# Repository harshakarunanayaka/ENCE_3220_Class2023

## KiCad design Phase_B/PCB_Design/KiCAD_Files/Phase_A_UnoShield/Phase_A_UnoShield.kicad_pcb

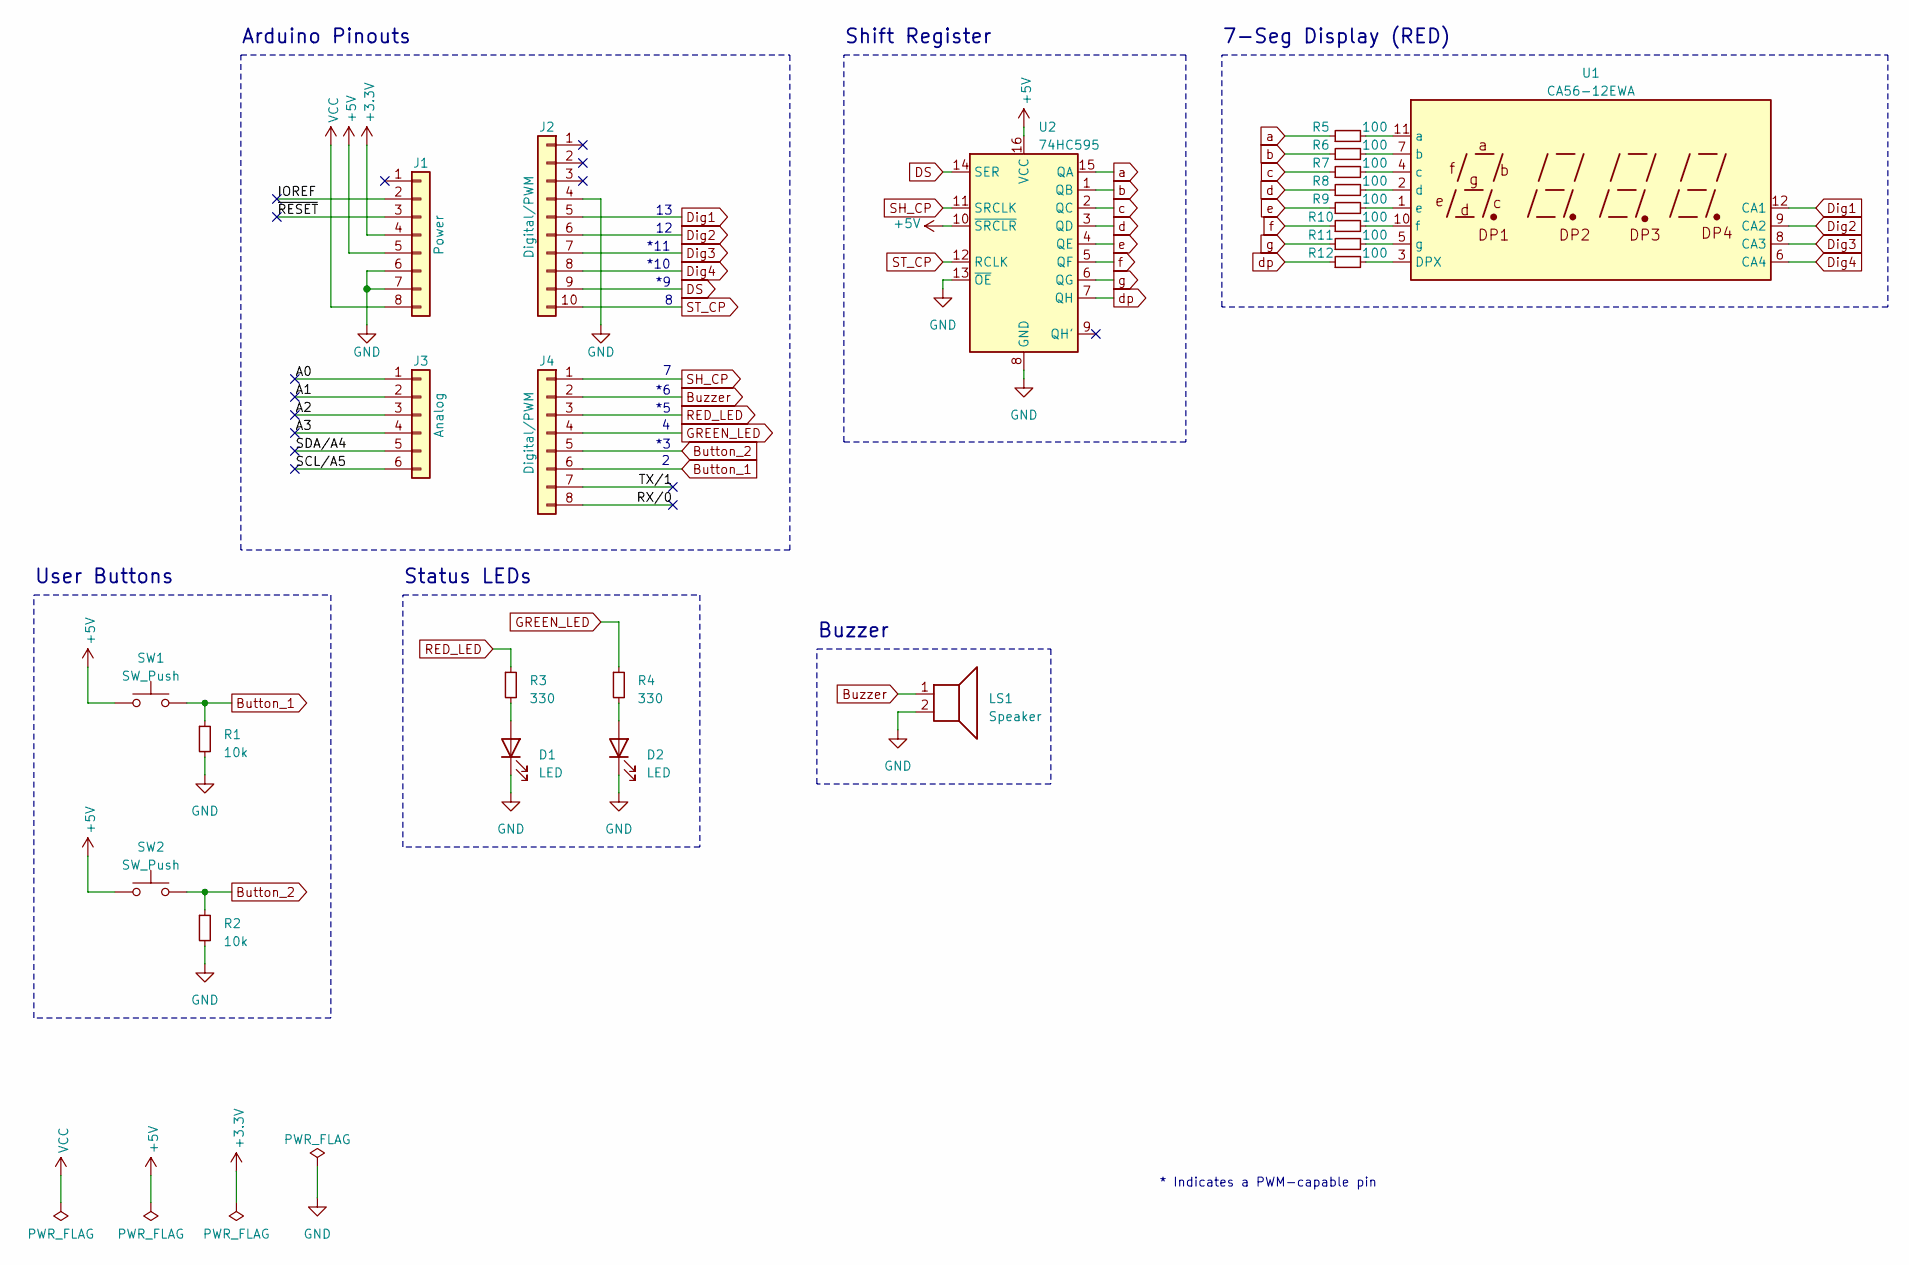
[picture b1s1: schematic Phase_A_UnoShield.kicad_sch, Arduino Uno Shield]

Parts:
D1, D2: LED; LED_D5.0mm
J1: Power; PinSocket_1x08_P2.54mm_Vertical
J2: Digital/PWM; PinSocket_1x10_P2.54mm_Vertical
J3: Analog; PinSocket_1x06_P2.54mm_Vertical
J4: Digital/PWM; PinSocket_1x08_P2.54mm_Vertical
LS1: Speaker; Buzzer_12x9.5RM7.6
R1, R2: 10k; R_Axial_DIN0207_L6.3mm_D2.5mm_P10.16mm_Horizontal
R3, R4: 330; R_Axial_DIN0207_L6.3mm_D2.5mm_P10.16mm_Horizontal
R5, R6, R7, R8, R9, R10, R11, R12: 100; R_Axial_DIN0207_L6.3mm_D2.5mm_P10.16mm_Horizontal
SW1, SW2: SW_Push; SW_PUSH-12mm
U1: CA56-12EWA
U2: 74HC595; DIP-16_W7.62mm_Socket_LongPads

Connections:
+3V3: J1.4
+5V: J1.5, SW1.1, SW2.1, U2.10 (~SRCLR), U2.16 (VCC)
/A0: J3.1
/A1: J3.2
/A2: J3.3
/A3: J3.4
/IOREF: J1.2
/RX/0: J4.8
/SCL/A5: J3.6
/SDA/A4: J3.5
/TX/1: J4.7
/~RESET: J1.3
Button_1: J4.6, R1.1, SW1.2
Button_2: J4.5, R2.1, SW2.2
Buzzer: J4.2, LS1.1
DS: J2.9, U2.14 (SER)
Dig1: J2.5, U1.12 (CA1)
Dig2: J2.6, U1.9 (CA2)
Dig3: J2.7, U1.8 (CA3)
Dig4: J2.8, U1.6 (CA4)
GND: D1.1 (K), D2.1 (K), J1.6, J1.7, J2.4, LS1.2, R1.2, R2.2, U2.8 (GND), U2.13 (~OE)
GREEN_LED: J4.4, R4.1
unnamed: D1.2 (A), R3.2
unnamed: D2.2 (A), R4.2
unnamed: R12.2, U1.3 (DPX)
unnamed: R5.2, U1.11 (a)
unnamed: R6.2, U1.7 (b)
unnamed: R7.2, U1.4 (c)
unnamed: R8.2, U1.2 (d)
unnamed: R9.2, U1.1 (e)
unnamed: R10.2, U1.10 (f)
unnamed: R11.2, U1.5 (g)
RED_LED: J4.3, R3.1
SH_CP: J4.1, U2.11 (SRCLK)
ST_CP: J2.10, U2.12 (RCLK)
VCC: J1.8
a: R5.1, U2.15 (QA)
b: R6.1, U2.1 (QB)
c: R7.1, U2.2 (QC)
d: R8.1, U2.3 (QD)
dp: R12.1, U2.7 (QH)
e: R9.1, U2.4 (QE)
f: R10.1, U2.5 (QF)
g: R11.1, U2.6 (QG)

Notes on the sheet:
Shift Register
*10
Status LEDs
Arduino Pinouts
User Buttons
Buzzer
* Indicates a PWM-capable pin
7-Seg Display (RED)
*11

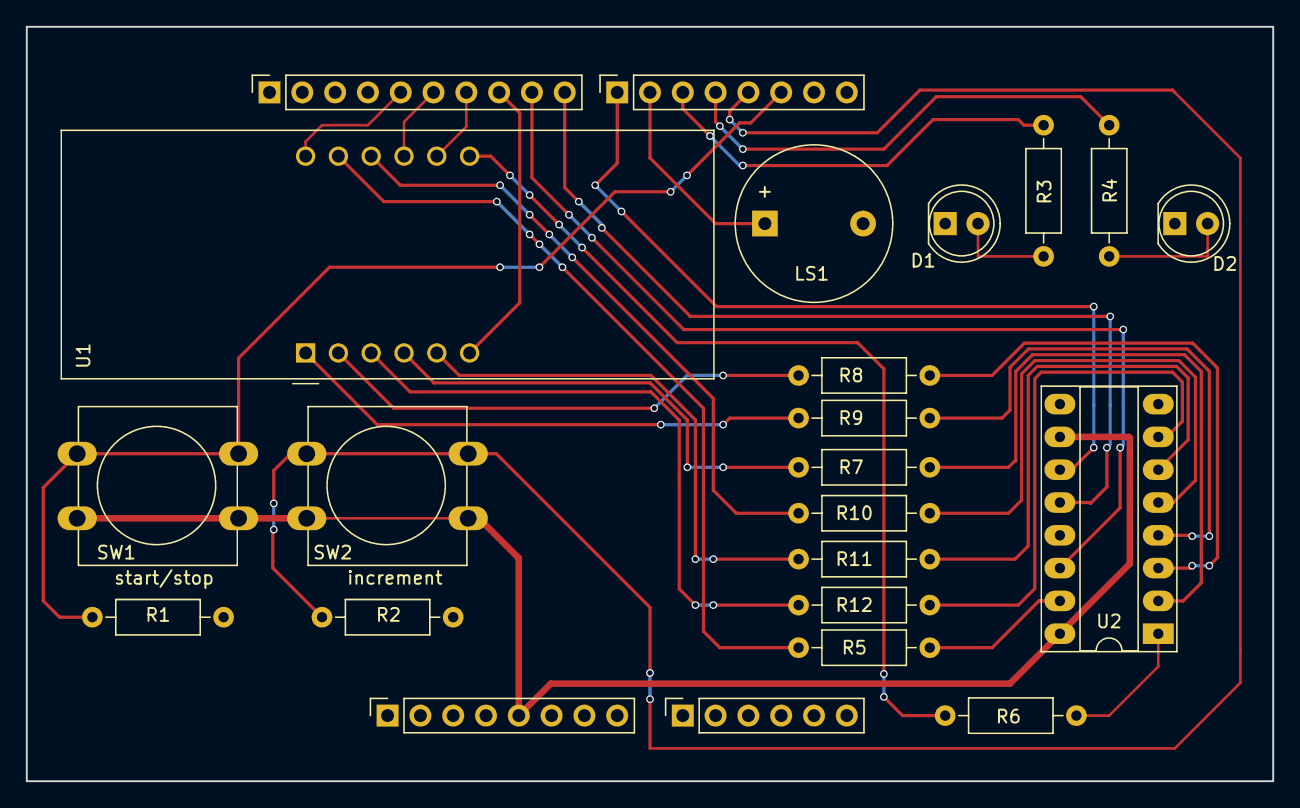
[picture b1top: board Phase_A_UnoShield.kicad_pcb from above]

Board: 2 copper layers, 96.5 x 58.4 mm, 23 parts (0 on the bottom side), 32 nets.

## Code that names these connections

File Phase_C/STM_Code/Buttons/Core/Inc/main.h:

/* USER CODE BEGIN Header */
/**
  ******************************************************************************
  * @file           : main.h
  * @brief          : Header for main.c file.
  *                   This file contains the common defines of the application.
  ******************************************************************************
  * @attention
  *
  * Copyright (c) 2023 STMicroelectronics.
  * All rights reserved.
  *
  * This software is licensed under terms that can be found in the LICENSE file
  * in the root directory of this software component.
  * If no LICENSE file comes with this software, it is provided AS-IS.
  *
  ******************************************************************************
  */
/* USER CODE END Header */

/* Define to prevent recursive inclusion -------------------------------------*/
#ifndef __MAIN_H
#define __MAIN_H

#ifdef __cplusplus
extern "C" {
#endif

/* Includes ------------------------------------------------------------------*/
#include "stm32f4xx_hal.h"

/* Private includes ----------------------------------------------------------*/
/* USER CODE BEGIN Includes */

/* USER CODE END Includes */

/* Exported types ------------------------------------------------------------*/
/* USER CODE BEGIN ET */

/* USER CODE END ET */

/* Exported constants --------------------------------------------------------*/
/* USER CODE BEGIN EC */

/* USER CODE END EC */

/* Exported macro ------------------------------------------------------------*/
/* USER CODE BEGIN EM */

/* USER CODE END EM */

/* Exported functions prototypes ---------------------------------------------*/
void Error_Handler(void);

/* USER CODE BEGIN EFP */

/* USER CODE END EFP */

/* Private defines -----------------------------------------------------------*/
#define CS_I2C_SPI_Pin GPIO_PIN_3
#define CS_I2C_SPI_GPIO_Port GPIOE
#define PC14_OSC32_IN_Pin GPIO_PIN_14
#define PC14_OSC32_IN_GPIO_Port GPIOC
#define PC15_OSC32_OUT_Pin GPIO_PIN_15
#define PC15_OSC32_OUT_GPIO_Port GPIOC
#define PH0_OSC_IN_Pin GPIO_PIN_0
#define PH0_OSC_IN_GPIO_Port GPIOH
#define PH1_OSC_OUT_Pin GPIO_PIN_1
#define PH1_OSC_OUT_GPIO_Port GPIOH
#define OTG_FS_PowerSwitchOn_Pin GPIO_PIN_0
#define OTG_FS_PowerSwitchOn_GPIO_Port GPIOC
#define PDM_OUT_Pin GPIO_PIN_3
#define PDM_OUT_GPIO_Port GPIOC
#define B1_Pin GPIO_PIN_0
#define B1_GPIO_Port GPIOA
#define B1_EXTI_IRQn EXTI0_IRQn
#define I2S3_WS_Pin GPIO_PIN_4
#define I2S3_WS_GPIO_Port GPIOA
#define SPI1_SCK_Pin GPIO_PIN_5
#define SPI1_SCK_GPIO_Port GPIOA
#define SPI1_MISO_Pin GPIO_PIN_6
#define SPI1_MISO_GPIO_Port GPIOA
#define SPI1_MOSI_Pin GPIO_PIN_7
#define SPI1_MOSI_GPIO_Port GPIOA
#define BUTTON_1_Pin GPIO_PIN_4
#define BUTTON_1_GPIO_Port GPIOC
#define BUTTON_1_EXTI_IRQn EXTI4_IRQn
#define BUTTON_2_Pin GPIO_PIN_5
#define BUTTON_2_GPIO_Port GPIOC
#define BUTTON_2_EXTI_IRQn EXTI9_5_IRQn
#define GREEN_LED_Pin GPIO_PIN_0
#define GREEN_LED_GPIO_Port GPIOB
#define RED_LED_Pin GPIO_PIN_1
#define RED_LED_GPIO_Port GPIOB
#define BOOT1_Pin GPIO_PIN_2
#define BOOT1_GPIO_Port GPIOB
#define CLOCK_Pin GPIO_PIN_7
#define CLOCK_GPIO_Port GPIOE
#define LATCH_Pin GPIO_PIN_8
#define LATCH_GPIO_Port GPIOE
#define DATA_Pin GPIO_PIN_9
#define DATA_GPIO_Port GPIOE
#define DIG4_Pin GPIO_PIN_11
#define DIG4_GPIO_Port GPIOE
#define DIG3_Pin GPIO_PIN_12
#define DIG3_GPIO_Port GPIOE
#define DIG2_Pin GPIO_PIN_13
#define DIG2_GPIO_Port GPIOE
#define DIG1_Pin GPIO_PIN_14
#define DIG1_GPIO_Port GPIOE
#define CLK_IN_Pin GPIO_PIN_10
#define CLK_IN_GPIO_Port GPIOB
#define LD4_Pin GPIO_PIN_12
#define LD4_GPIO_Port GPIOD
#define LD3_Pin GPIO_PIN_13
#define LD3_GPIO_Port GPIOD
#define LD5_Pin GPIO_PIN_14
#define LD5_GPIO_Port GPIOD
#define LD6_Pin GPIO_PIN_15
#define LD6_GPIO_Port GPIOD
#define I2S3_MCK_Pin GPIO_PIN_7
#define I2S3_MCK_GPIO_Port GPIOC
#define VBUS_FS_Pin GPIO_PIN_9
#define VBUS_FS_GPIO_Port GPIOA
#define OTG_FS_ID_Pin GPIO_PIN_10
#define OTG_FS_ID_GPIO_Port GPIOA
#define OTG_FS_DM_Pin GPIO_PIN_11
#define OTG_FS_DM_GPIO_Port GPIOA
#define OTG_FS_DP_Pin GPIO_PIN_12
#define OTG_FS_DP_GPIO_Port GPIOA
#define SWDIO_Pin GPIO_PIN_13
#define SWDIO_GPIO_Port GPIOA
#define SWCLK_Pin GPIO_PIN_14
#define SWCLK_GPIO_Port GPIOA
#define I2S3_SCK_Pin GPIO_PIN_10
#define I2S3_SCK_GPIO_Port GPIOC
#define I2S3_SD_Pin GPIO_PIN_12
#define I2S3_SD_GPIO_Port GPIOC
#define Audio_RST_Pin GPIO_PIN_4
#define Audio_RST_GPIO_Port GPIOD
#define OTG_FS_OverCurrent_Pin GPIO_PIN_5
#define OTG_FS_OverCurrent_GPIO_Port GPIOD
#define SWO_Pin GPIO_PIN_3
#define SWO_GPIO_Port GPIOB
#define Audio_SCL_Pin GPIO_PIN_6
#define Audio_SCL_GPIO_Port GPIOB
#define Audio_SDA_Pin GPIO_PIN_9
#define Audio_SDA_GPIO_Port GPIOB
#define MEMS_INT2_Pin GPIO_PIN_1
#define MEMS_INT2_GPIO_Port GPIOE

/* USER CODE BEGIN Private defines */

/* USER CODE END Private defines */

#ifdef __cplusplus
}
#endif

#endif /* __MAIN_H */

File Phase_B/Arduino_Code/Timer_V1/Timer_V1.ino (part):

#define BUTTON_2  2  // Inc Timer
#define BUTTON_1  3  // Start/Stop Timer and Stop Buzzer
#define GREEN_LED 4
#define RED_LED   5
#define BUZZER    6

#define DATA      9 // DS
#define LATCH     8 // ST_CP
#define CLOCK     7 // SH_CP

#define DIGIT_4   10
#define DIGIT_3   11
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  Serial.begin(9600);
  
  // LEDs Pins
  pinMode(RED_LED, OUTPUT);
  pinMode(GREEN_LED, OUTPUT);

  // LEDs -> Timer Stopped
  digitalWrite(RED_LED, HIGH);
  digitalWrite(GREEN_LED, HIGH);

  // Button Pins
  pinMode(BUTTON_1, INPUT_PULLUP);
  attachInterrupt(digitalPinToInterrupt(BUTTON_1), buttonISR1, RISING);
  pinMode(BUTTON_2, INPUT_PULLUP);
  attachInterrupt(digitalPinToInterrupt(BUTTON_2), buttonISR2, RISING);

  // Buzer Pins
  pinMode(BUZZER, OUTPUT);

  // Buzzer -> Off
  digitalWrite(BUZZER,LOW);
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
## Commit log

2023-04-12 Create code
2023-04-12 Create pp
2023-04-12 Create n
2023-04-17 Phase_B_Updated
2023-04-17 Phase_B
2023-04-17 Phase_A
2023-05-13 Phase_C
2023-06-01 Phase_D
